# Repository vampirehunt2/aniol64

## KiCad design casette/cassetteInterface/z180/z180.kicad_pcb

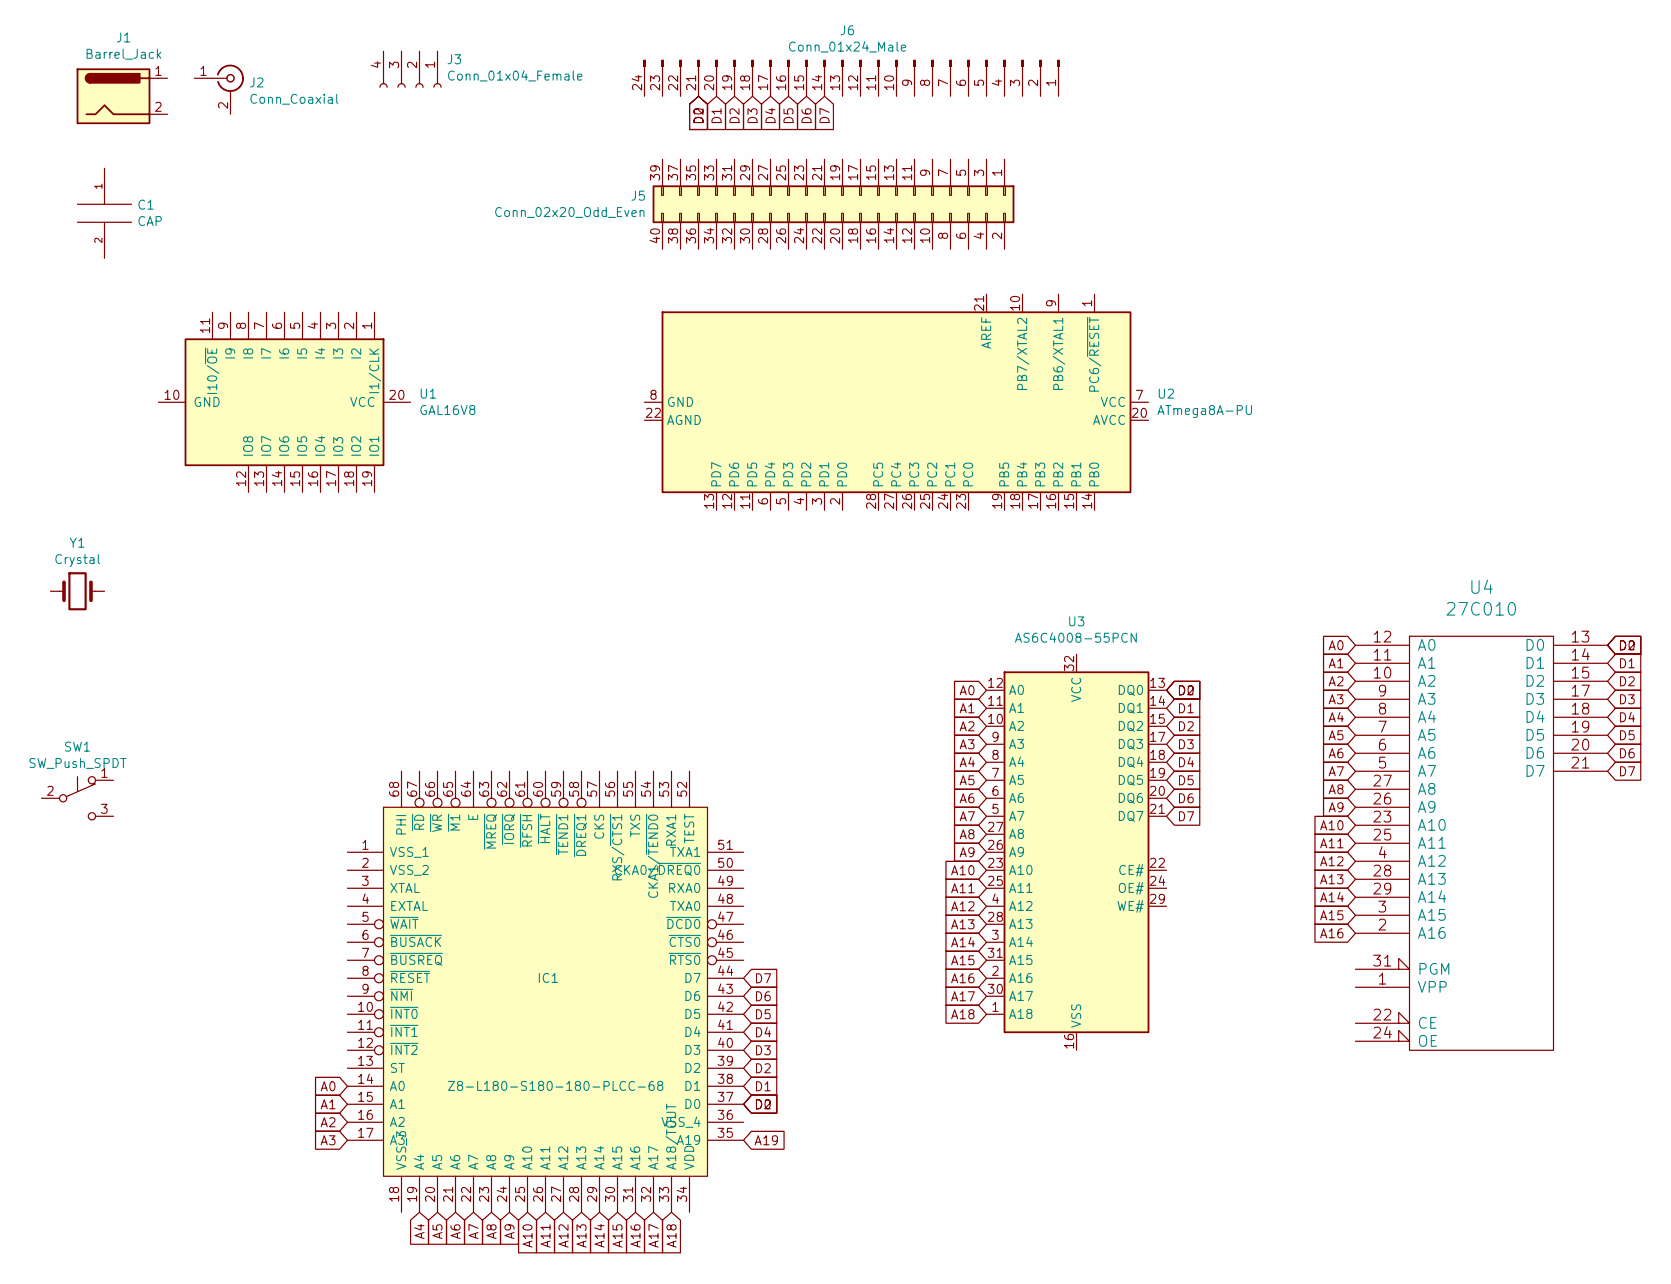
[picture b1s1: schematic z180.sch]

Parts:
C1: CAP; CP_Radial_D10.0mm_P5.00mm_P7.50mm
IC1: Z8-L180-S180-180-PLCC-68; PLCC-68; Manufacturer_Part_Number Z8S18033VSG; Mouser Part Number 692-Z8S18033VSG
J1: Barrel_Jack; BarrelJack_Horizontal
J2: Conn_Coaxial; SMA_Amphenol_132203-12_Horizontal
J3: Conn_01x04_Female; PinHeader_1x04_P2.54mm_Horizontal
J5: Conn_02x20_Odd_Even; PinHeader_2x20_P2.54mm_Vertical_SMD
J6: Conn_01x24_Male; PinHeader_1x24_P2.54mm_Horizontal
SW1: SW_Push_SPDT; SW_Tactile_SKHH_Angled
U1: GAL16V8; DIP-20_W7.62mm_Socket
U2: ATmega8A-PU; DIP-28_W7.62mm
U3: AS6C4008-55PCN; DIP-32_W15.24mm
U4: 27C010; DIP-32_W15.24mm
Y1: Crystal; Crystal_AT310_D3.0mm_L10.0mm_Vertical

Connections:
A0: IC1.14 (A0), U3.12 (A0), U4.12 (A0)
A1: IC1.15 (A1), U3.11 (A1), U4.11 (A1)
A2: IC1.16 (A2), U3.10 (A2), U4.10 (A2)
A3: IC1.17 (A3), U3.9 (A3), U4.9 (A3)
A4: IC1.19 (A4), U3.8 (A4), U4.8 (A4)
A5: IC1.20 (A5), U3.7 (A5), U4.7 (A5)
A6: IC1.21 (A6), U3.6 (A6), U4.6 (A6)
A7: IC1.22 (A7), U3.5 (A7), U4.5 (A7)
A8: IC1.23 (A8), U3.27 (A8), U4.27 (A8)
A9: IC1.24 (A9), U3.26 (A9), U4.26 (A9)
A10: IC1.25 (A10), U3.23 (A10), U4.23 (A10)
A11: IC1.26 (A11), U3.25 (A11), U4.25 (A11)
A12: IC1.27 (A12), U3.4 (A12), U4.4 (A12)
A13: IC1.28 (A13), U3.28 (A13), U4.28 (A13)
A14: IC1.29 (A14), U3.3 (A14), U4.29 (A14)
A15: IC1.30 (A15), U3.31 (A15), U4.3 (A15)
A16: IC1.31 (A16), U3.2 (A16), U4.2 (A16)
A17: IC1.32 (A17), U3.30 (A17)
A18: IC1.33 (A18/TOUT), U3.1 (A18)
D0: IC1.37 (D0), IC1.39 (D2), J6.19, J6.21, U3.13 (DQ0), U3.15 (DQ2), U4.13 (D0), U4.15 (D2)
D1: IC1.38 (D1), J6.20, U3.14 (DQ1), U4.14 (D1)
D3: IC1.40 (D3), J6.18, U3.17 (DQ3), U4.17 (D3)
D4: IC1.41 (D4), J6.17, U3.18 (DQ4), U4.18 (D4)
D5: IC1.42 (D5), J6.16, U3.19 (DQ5), U4.19 (D5)
D6: IC1.43 (D6), J6.15, U3.20 (DQ6), U4.20 (D6)
D7: IC1.44 (D7), J6.14, U3.21 (DQ7), U4.21 (D7)

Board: 2 copper layers, 13 parts (0 on the bottom side), 26 nets, no tracks yet.

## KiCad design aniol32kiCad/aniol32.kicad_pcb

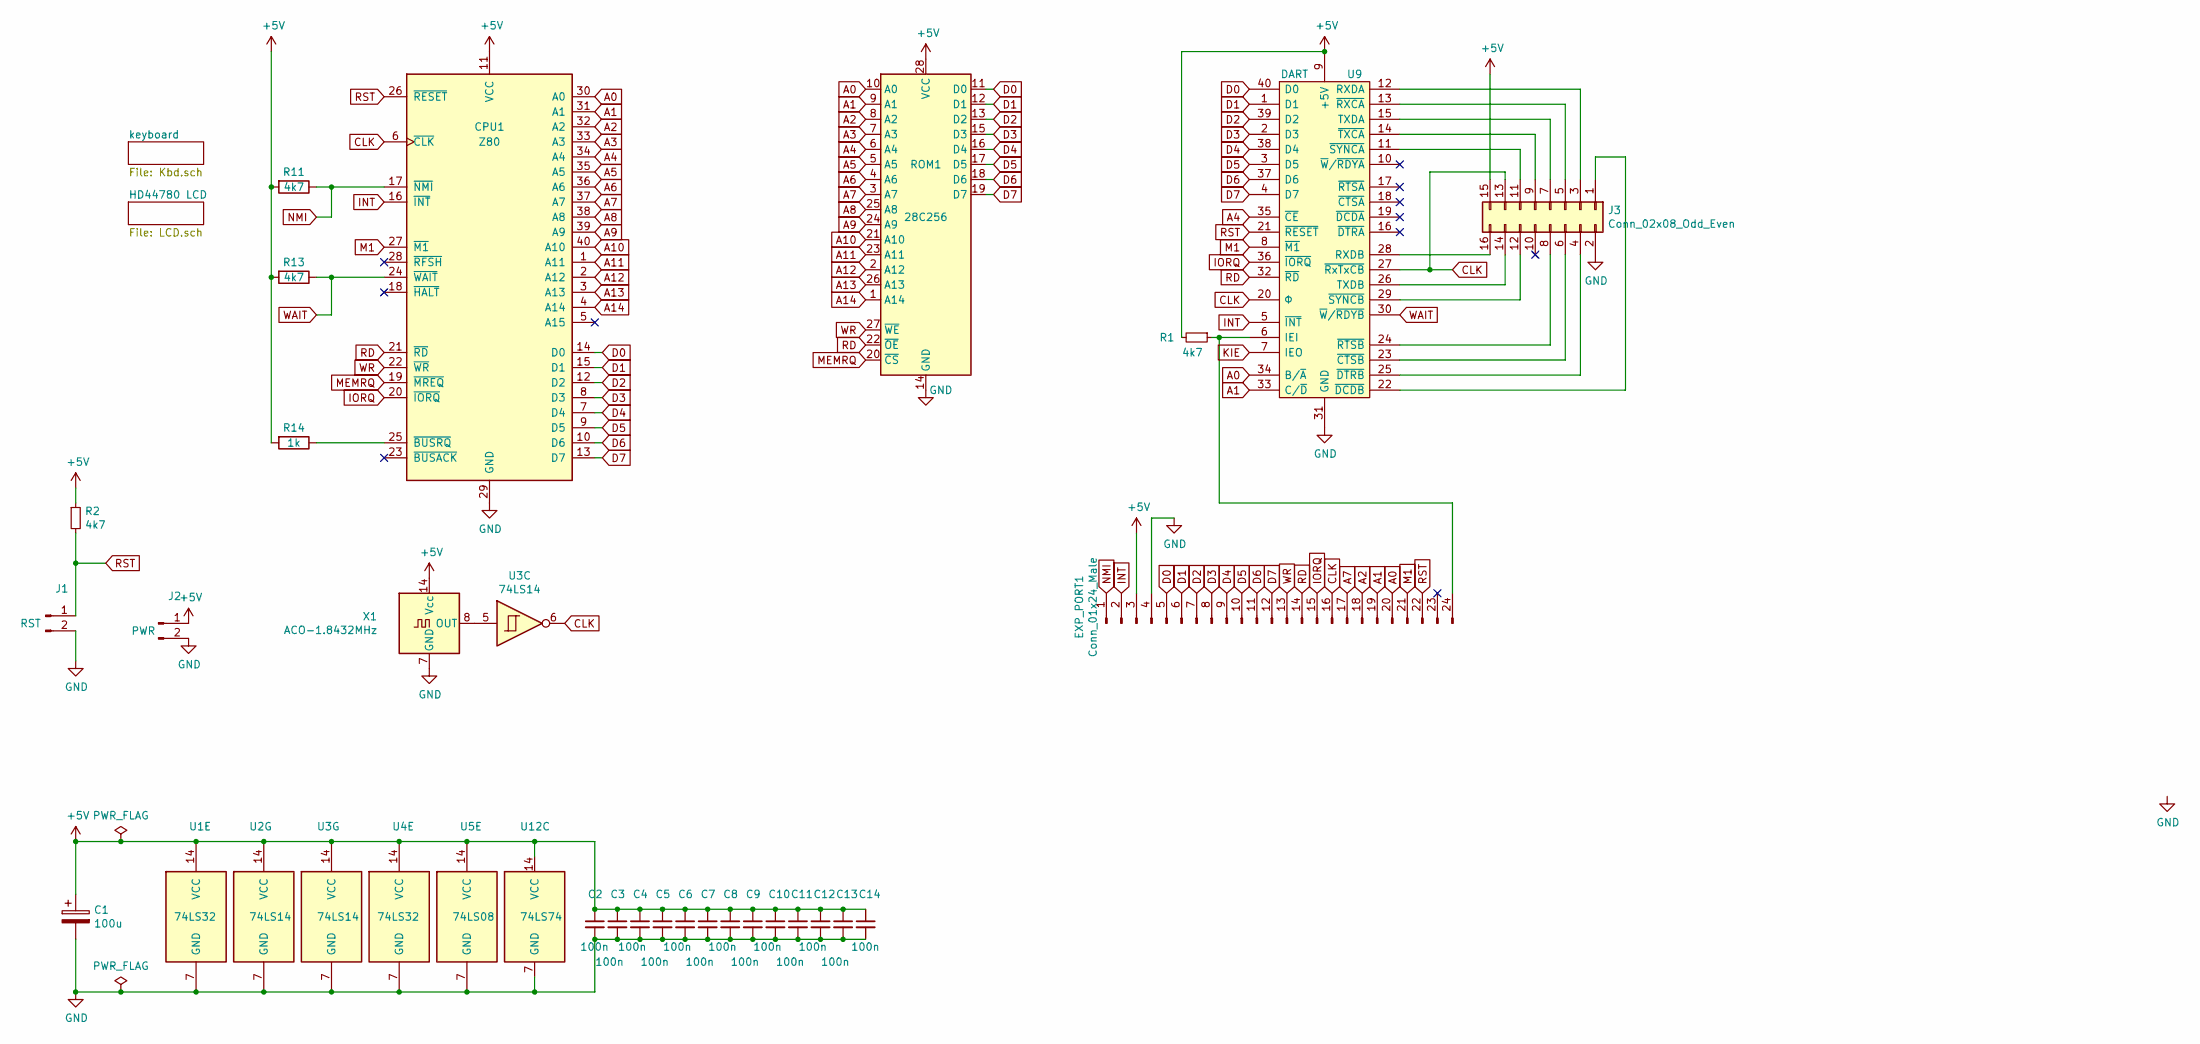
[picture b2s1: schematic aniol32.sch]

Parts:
C1: 100u; CP_Radial_D14.0mm_P7.50mm
C2, C3, C4, C5, C6, C7, C8, C9, C10, C11, C12, C13, C14: 100n; C_Disc_D5.0mm_W2.5mm_P5.00mm
CPU1: Z80; DIP-40_W15.24mm_Socket
EXP_PORT1: Conn_01x24_Male; PinHeader_1x24_P2.54mm_Horizontal
J1: RST; PinHeader_1x02_P2.54mm_Vertical
J2: PWR; PinHeader_1x02_P2.54mm_Vertical
J3: Conn_02x08_Odd_Even; PinSocket_2x08_P2.54mm_Horizontal
R1, R2, R11, R13: 4k7; R_Axial_DIN0207_L6.3mm_D2.5mm_P7.62mm_Horizontal
R14: 1k; R_Axial_DIN0207_L6.3mm_D2.5mm_P7.62mm_Horizontal
ROM1: 28C256; DIP-28_W15.24mm_Socket
U1, U4: 74LS32; DIP-14_W7.62mm_Socket
U2, U3: 74LS14; DIP-14_W7.62mm_Socket
U5: 74LS08; DIP-14_W7.62mm_Socket
U9: DART; DIP-40_W15.24mm_Socket; Manufacturer_Part_Number Z84C4206PEG; Mouser Part Number 692-Z84C4206PEG
U12: 74LS74; DIP-14_W7.62mm_Socket
X1: ACO-1.8432MHz; Oscillator_DIP-14

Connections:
+5V: C1.1, C2.1, C3.1, C4.1, C5.1, C6.1, C7.1, C8.1, C9.1, C10.1, C11.1, C12.1, C13.1, C14.1, CPU1.11 (VCC), EXP_PORT1.3, J2.1, J3.15, R1.2, R2.1, R11.2, R13.2, R14.2, ROM1.28 (VCC), U1.14 (VCC), U2.14 (VCC), U3.14 (VCC), U4.14 (VCC), U5.14 (VCC), U9.9 (+5V), U12.14 (VCC), X1.14 (Vcc); also elsewhere on the board
A0: CPU1.30 (A0), EXP_PORT1.20, ROM1.10 (A0), U9.34 (B/~A); also elsewhere on the board
A1: CPU1.31 (A1), EXP_PORT1.19, ROM1.9 (A1), U9.33 (C/~D); also elsewhere on the board
A2: CPU1.32 (A2), EXP_PORT1.18, ROM1.8 (A2)
A3: CPU1.33 (A3), ROM1.7 (A3), U1.10
A4: CPU1.34 (A4), ROM1.6 (A4), U9.35 (~CE)
A5: CPU1.35 (A5), ROM1.5 (A5)
A6: CPU1.36 (A6), ROM1.4 (A6); also elsewhere on the board
A7: CPU1.37 (A7), EXP_PORT1.17, ROM1.3 (A7)
A8: CPU1.38 (A8), ROM1.25 (A8)
A9: CPU1.39 (A9), ROM1.24 (A9)
A10: CPU1.40 (A10), ROM1.21 (A10)
A11: CPU1.1 (A11), ROM1.23 (A11)
A12: CPU1.2 (A12), ROM1.2 (A12)
A13: CPU1.3 (A13), ROM1.26 (A13)
A14: CPU1.4 (A14), ROM1.1 (A14)
CLK: CPU1.6 (~CLK~), EXP_PORT1.16, J3.13, U3.6, U9.20 (Φ), U9.27 (~RxTxCB); also elsewhere on the board
D0: CPU1.14 (D0), EXP_PORT1.5, ROM1.11 (D0), U9.40 (D0); also elsewhere on the board
D1: CPU1.15 (D1), EXP_PORT1.6, ROM1.12 (D1), U9.1 (D1); also elsewhere on the board
D2: CPU1.12 (D2), EXP_PORT1.7, ROM1.13 (D2), U9.39 (D2); also elsewhere on the board
D3: CPU1.8 (D3), EXP_PORT1.8, ROM1.15 (D3), U9.2 (D3); also elsewhere on the board
D4: CPU1.7 (D4), EXP_PORT1.9, ROM1.16 (D4), U9.38 (D4); also elsewhere on the board
D5: CPU1.9 (D5), EXP_PORT1.10, ROM1.17 (D5), U9.3 (D5); also elsewhere on the board
D6: CPU1.10 (D6), EXP_PORT1.11, ROM1.18 (D6), U9.37 (D6); also elsewhere on the board
D7: CPU1.13 (D7), EXP_PORT1.12, ROM1.19 (D7), U9.4 (D7); also elsewhere on the board
GND: C1.2, C2.2, C3.2, C4.2, C5.2, C6.2, C7.2, C8.2, C9.2, C10.2, C11.2, C12.2, C13.2, C14.2, CPU1.29 (GND), EXP_PORT1.4, J1.2, J2.2, J3.2, ROM1.14 (GND), U1.7 (GND), U2.7 (GND), U3.7 (GND), U4.7 (GND), U5.7 (GND), U9.31 (GND), U12.7 (GND), X1.7 (GND); also elsewhere on the board
INT: CPU1.16 (~INT~), EXP_PORT1.2, U9.5 (~INT); also elsewhere on the board
IORQ: CPU1.20 (~IORQ~), EXP_PORT1.15, U1.9, U9.36 (~IORQ); also elsewhere on the board
KIE: U9.7 (IEO); also elsewhere on the board
LCDE: U2.4; also elsewhere on the board
M1: CPU1.27 (~M1~), EXP_PORT1.21, U9.8 (~M1); also elsewhere on the board
MEMRQ: CPU1.19 (~MREQ~), ROM1.20 (~CS)
NMI: CPU1.17 (~NMI~), EXP_PORT1.1, R11.1; also elsewhere on the board
unnamed: CPU1.25 (~BUSRQ~), R14.1
unnamed: EXP_PORT1.24, R1.1, U9.6 (IEI)
unnamed: J3.3, U9.12 (RXDA)
unnamed: J3.4, U9.25 (~DTRB)
unnamed: J3.5, U9.13 (~RXCA)
unnamed: J3.6, U9.23 (~CTSB)
unnamed: J3.7, U9.15 (TXDA)
unnamed: J3.8, U9.24 (~RTSB)
unnamed: J3.9, U9.14 (~TXCA)
unnamed: J3.11, U9.11 (~SYNCA)
unnamed: J3.12, U9.29 (~SYNCB)
unnamed: J3.16, U9.28 (RXDB)
unnamed: U1.11, U2.3
unnamed: U1.8, U1.12
unnamed: U1.13, U5.11
unnamed: U3.5, X1.8 (OUT)
RD: CPU1.21 (~RD~), EXP_PORT1.14, ROM1.22 (~OE), U5.12, U9.32 (~RD); also elsewhere on the board
RST: CPU1.26 (~RESET~), EXP_PORT1.22, J1.1, R2.2, U9.21 (~RESET); also elsewhere on the board
WAIT: CPU1.24 (~WAIT~), R13.1, U9.30 (~W~/~RDYB)
WR: CPU1.22 (~WR~), EXP_PORT1.13, ROM1.27 (~WE), U5.13; also elsewhere on the board

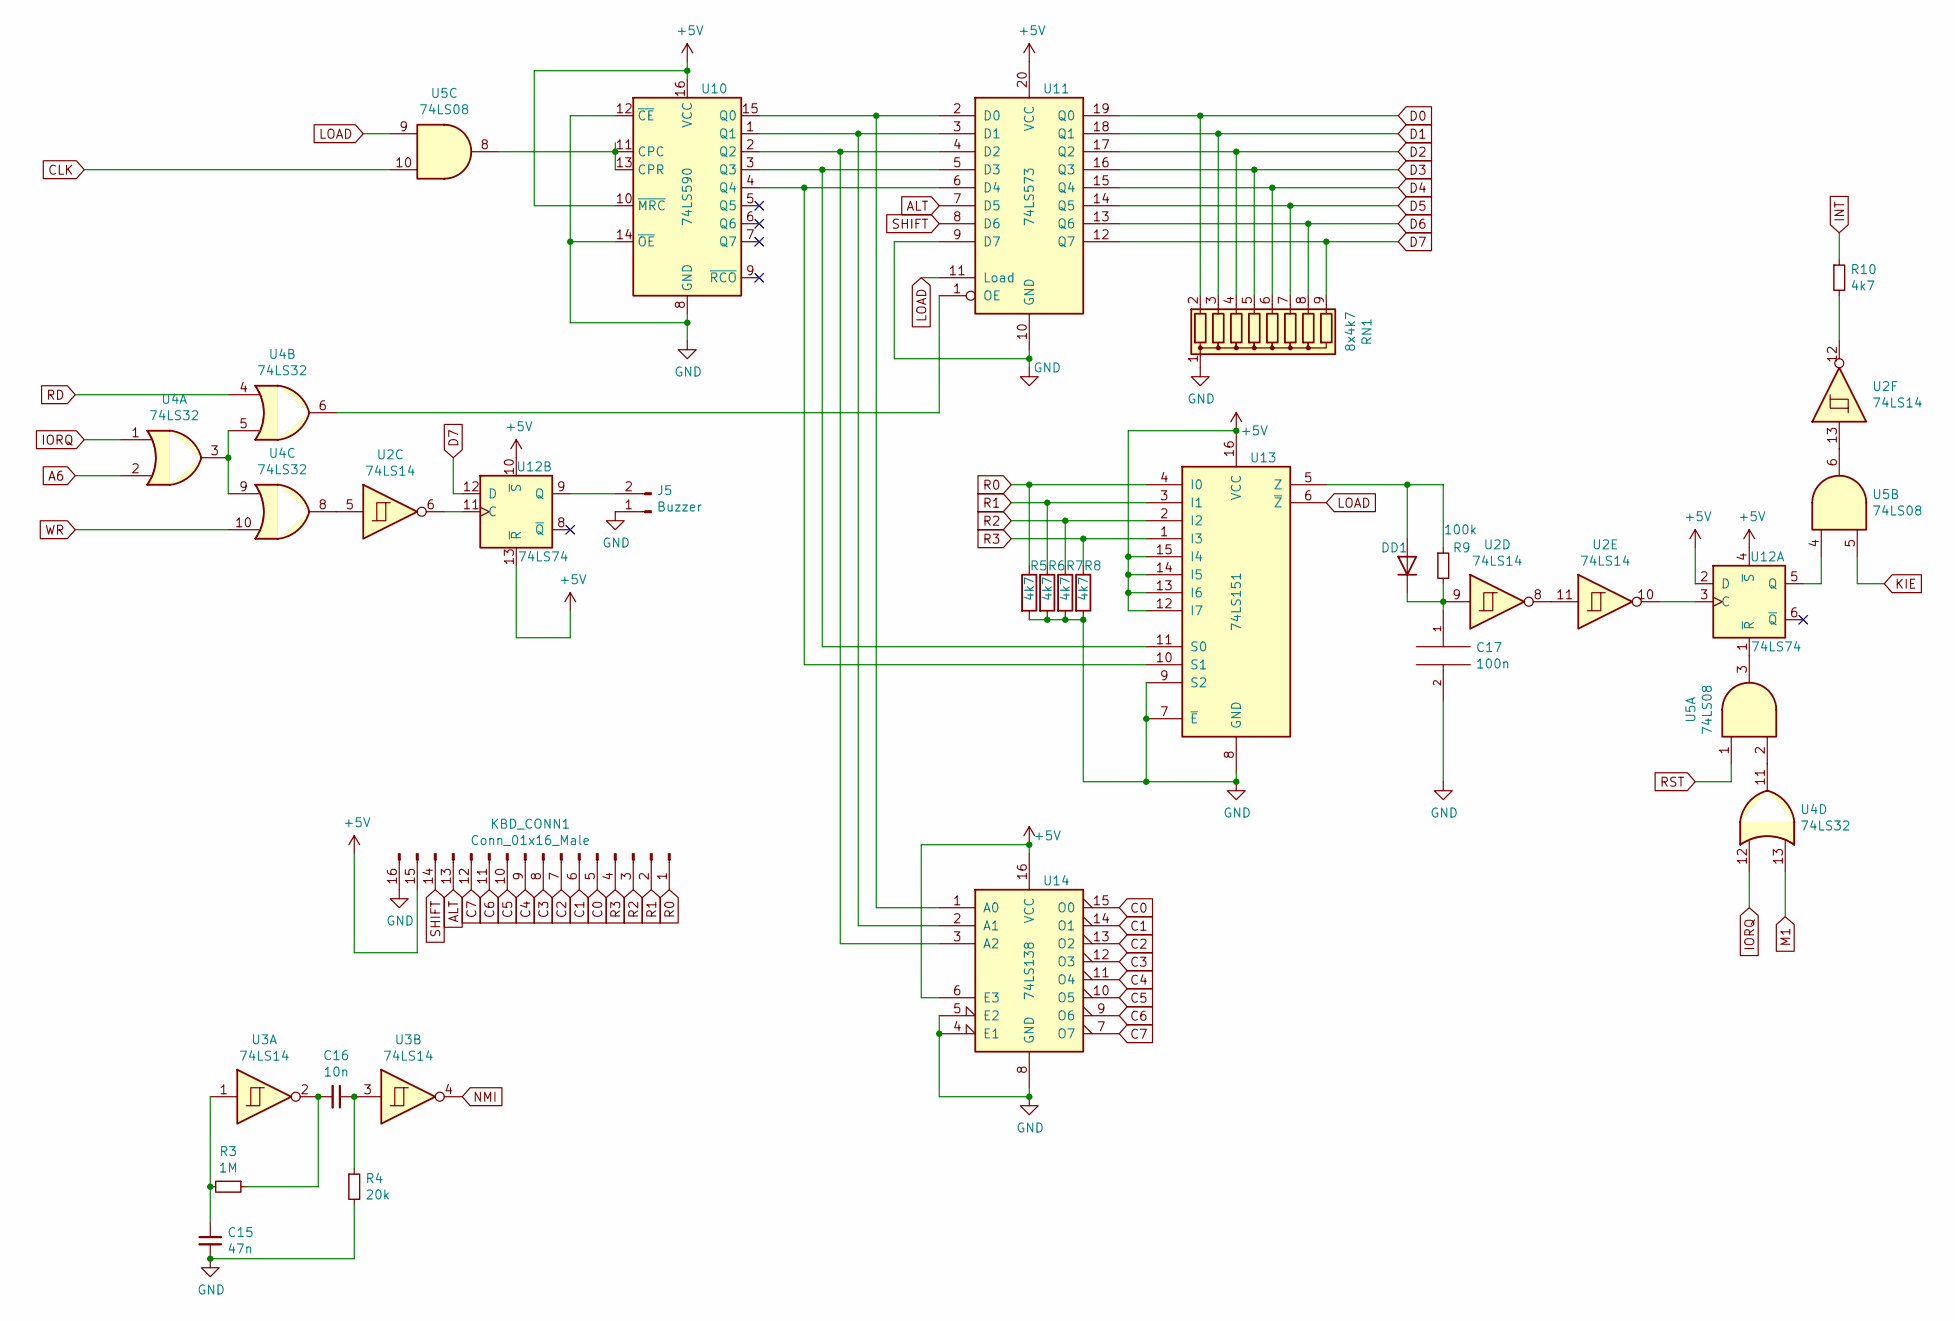
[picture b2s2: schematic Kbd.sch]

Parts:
C15: 47n; C_Disc_D5.0mm_W2.5mm_P5.00mm
C16: 10n; C_Disc_D5.0mm_W2.5mm_P5.00mm
C17: 100n; C_Disc_D5.0mm_W2.5mm_P5.00mm
D1: D; D_5KPW_P7.62mm_Vertical_AnodeUp
J5: Buzzer; PinHeader_1x02_P2.54mm_Vertical
KBD_CONN1: Conn_01x16_Male; PinHeader_1x16_P2.54mm_Vertical
R3: 1M; R_Axial_DIN0207_L6.3mm_D2.5mm_P7.62mm_Horizontal
R4: 20k; R_Axial_DIN0207_L6.3mm_D2.5mm_P7.62mm_Horizontal
R5, R6, R7, R8, R10: 4k7; R_Axial_DIN0207_L6.3mm_D2.5mm_P7.62mm_Horizontal
R9: 100k; R_Axial_DIN0207_L6.3mm_D2.5mm_P7.62mm_Horizontal
RN1: 8x4k7; R_Array_SIP9
U2, U3: 74LS14; DIP-14_W7.62mm_Socket
U4: 74LS32; DIP-14_W7.62mm_Socket
U5: 74LS08; DIP-14_W7.62mm_Socket
U10: 74LS590; DIP-16_W7.62mm_Socket
U11: 74LS573; DIP-20_W7.62mm_Socket
U12: 74LS74; DIP-14_W7.62mm_Socket
U13: 74LS151; DIP-16_W7.62mm_Socket
U14: 74LS138; DIP-16_W7.62mm_Socket

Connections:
+5V: KBD_CONN1.15, U10.10 (~MRC), U10.16 (VCC), U11.20 (VCC), U12.2 (D), U12.4 (~S), U12.10 (~S), U12.13 (~R), U13.12 (I7), U13.13 (I6), U13.14 (I5), U13.15 (I4), U13.16 (VCC), U14.6 (E3), U14.16 (VCC); also elsewhere on the board
A6: U4.2; also elsewhere on the board
ALT: KBD_CONN1.13, U11.7 (D5)
C0: KBD_CONN1.5, U14.15 (O0)
C1: KBD_CONN1.6, U14.14 (O1)
C2: KBD_CONN1.7, U14.13 (O2)
C3: KBD_CONN1.8, U14.12 (O3)
C4: KBD_CONN1.9, U14.11 (O4)
C5: KBD_CONN1.10, U14.10 (O5)
C6: KBD_CONN1.11, U14.9 (O6)
C7: KBD_CONN1.12, U14.7 (O7)
CLK: U5.10; also elsewhere on the board
D0: RN1.2 (R1), U11.19 (Q0); also elsewhere on the board
D1: RN1.3 (R2), U11.18 (Q1); also elsewhere on the board
D2: RN1.4 (R3), U11.17 (Q2); also elsewhere on the board
D3: RN1.5 (R4), U11.16 (Q3); also elsewhere on the board
D4: RN1.6 (R5), U11.15 (Q4); also elsewhere on the board
D5: RN1.7 (R6), U11.14 (Q5); also elsewhere on the board
D6: RN1.8 (R7), U11.13 (Q6); also elsewhere on the board
D7: RN1.9 (R8), U11.12 (Q7), U12.12 (D); also elsewhere on the board
GND: C15.2, C17.2, J5.1, KBD_CONN1.16, R4.2, R5.2, R6.2, R7.2, R8.2, RN1.1 (common), U10.8 (GND), U10.12 (~CE), U10.14 (~OE), U11.9 (D7), U11.10 (GND), U13.7 (~E), U13.8 (GND), U13.9 (S2), U14.4 (E1), U14.5 (E2), U14.8 (GND); also elsewhere on the board
INT: R10.1; also elsewhere on the board
IORQ: U4.1, U4.12; also elsewhere on the board
KIE: U5.5; also elsewhere on the board
LCDE: U2.4; also elsewhere on the board
LOAD: U5.9, U11.11 (Load), U13.6 (~Z)
M1: U4.13; also elsewhere on the board
NMI: U3.4; also elsewhere on the board
unnamed: C15.1, R3.2, U3.1
unnamed: C16.1, R4.1, U3.3
unnamed: C16.2, R3.1, U3.2
unnamed: C17.1, D1.1 (K), R9.2, U2.9
unnamed: D1.2 (A), R9.1, U13.5 (Z)
unnamed: J5.2, U12.9 (Q)
unnamed: R10.2, U2.12
unnamed 63: U2.3; also elsewhere on the board
unnamed 65: U5.11; also elsewhere on the board
unnamed: U2.5, U4.8
unnamed: U2.8, U2.11
unnamed: U2.13, U5.6
unnamed: U4.3, U4.5, U4.9
unnamed: U4.11, U5.2
unnamed: U10.1 (Q1), U11.3 (D1), U14.2 (A1)
unnamed: U10.2 (Q2), U11.4 (D2), U14.3 (A2)
unnamed: U10.3 (Q3), U11.5 (D3), U13.11 (S0)
unnamed: U10.4 (Q4), U11.6 (D4), U13.10 (S1)
unnamed: U5.8, U10.11 (CPC), U10.13 (CPR)
unnamed: U10.15 (Q0), U11.2 (D0), U14.1 (A0)
unnamed: U4.6, U11.1 (OE)
unnamed: U5.3, U12.1 (~R)
unnamed: U2.10, U12.3 (C)
unnamed: U5.4, U12.5 (Q)
unnamed: U2.6, U12.11 (C)
R0: KBD_CONN1.1, R5.1, U13.4 (I0)
R1: KBD_CONN1.2, R6.1, U13.3 (I1)
R2: KBD_CONN1.3, R7.1, U13.2 (I2)
R3: KBD_CONN1.4, R8.1, U13.1 (I3)
RD: U4.4, U5.12; also elsewhere on the board
RST: U5.1; also elsewhere on the board
SHIFT: KBD_CONN1.14, U11.8 (D6)
WR: U4.10, U5.13; also elsewhere on the board

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
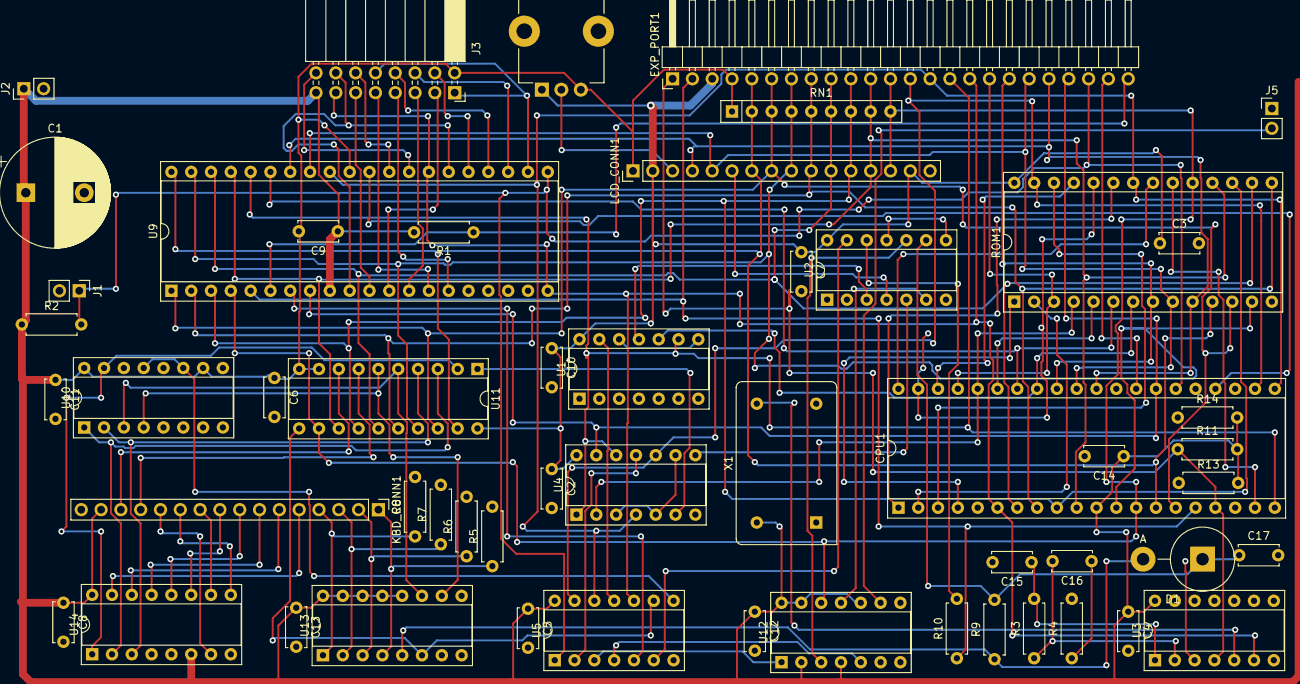
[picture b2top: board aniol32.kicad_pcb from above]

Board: 2 copper layers, 54 parts (0 on the bottom side), 94 nets.

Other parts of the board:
LCD_CONN1: Conn_01x16_Male; PinHeader_1x16_P2.54mm_Vertical
RV1: R_POT_TRIM; Potentiometer_TT_P0915N

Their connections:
+5V: LCD_CONN1.2, LCD_CONN1.15, RV1.1; also elsewhere on the board
A0: LCD_CONN1.4; also elsewhere on the board
A1: LCD_CONN1.5; also elsewhere on the board
CONTRAST: LCD_CONN1.3, RV1.2
D0: LCD_CONN1.7; also elsewhere on the board
D1: LCD_CONN1.8; also elsewhere on the board
D2: LCD_CONN1.9; also elsewhere on the board
D3: LCD_CONN1.10; also elsewhere on the board
D4: LCD_CONN1.11; also elsewhere on the board
D5: LCD_CONN1.12; also elsewhere on the board
D6: LCD_CONN1.13; also elsewhere on the board
D7: LCD_CONN1.14; also elsewhere on the board
GND: LCD_CONN1.1, LCD_CONN1.16, RV1.3; also elsewhere on the board
LCDE: LCD_CONN1.6; also elsewhere on the board

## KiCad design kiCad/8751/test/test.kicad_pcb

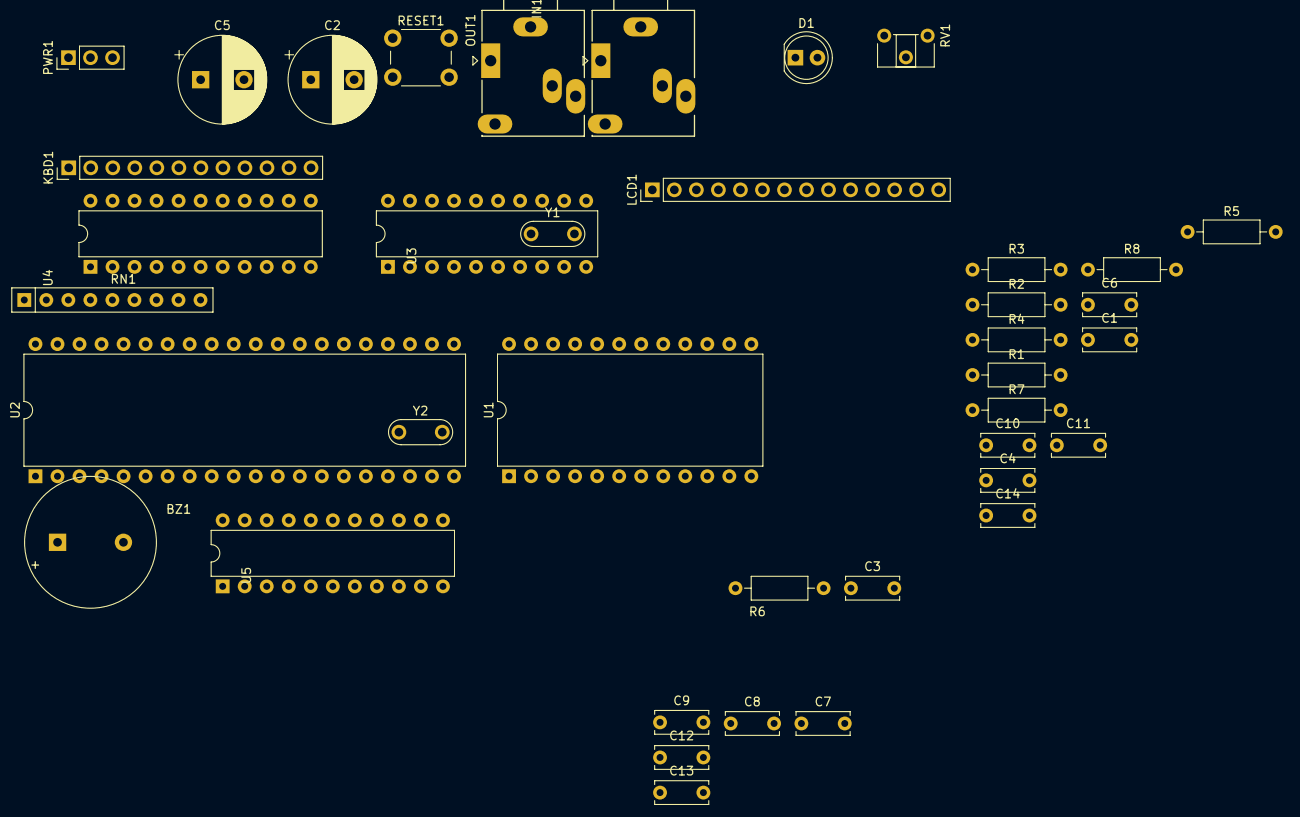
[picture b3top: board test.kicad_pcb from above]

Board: 2 copper layers, 39 parts (0 on the bottom side), 67 nets, no tracks yet.

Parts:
BZ1: Buzzer; Buzzer_15x7.5RM7.6
C1, C6, C7, C9, C10, C12, C13, C14: 100n; C_Disc_D6.0mm_W2.5mm_P5.00mm
C2, C5: C_Polarized; CP_Radial_D10.0mm_P5.00mm
C3, C4: 27p; C_Disc_D6.0mm_W2.5mm_P5.00mm
C8, C11: 18p; C_Disc_D6.0mm_W2.5mm_P5.00mm
D1: LED; LED_D5.0mm
IN1: AudioJack3; Jack_3.5mm_Ledino_KB3SPRS_Horizontal
KBD1: KBD; PinHeader_1x12_P2.54mm_Vertical
LCD1: LCD; PinHeader_1x14_P2.54mm_Vertical
OUT1: AudioJack3; Jack_3.5mm_Ledino_KB3SPRS_Horizontal
PWR1: Conn_01x03_Male; PinHeader_1x03_P2.54mm_Vertical
R1: 10k; R_Axial_DIN0207_L6.3mm_D2.5mm_P10.16mm_Horizontal
R2, R3: R_Small; R_Axial_DIN0207_L6.3mm_D2.5mm_P10.16mm_Horizontal
R4: 600; R_Axial_DIN0207_L6.3mm_D2.5mm_P10.16mm_Horizontal
R5, R6, R7, R8: 1k; R_Axial_DIN0207_L6.3mm_D2.5mm_P10.16mm_Horizontal
RESET1: SW_SPST; SW_PUSH_6mm
RN1: 470; R_Array_SIP9
RV1: 5k; Potentiometer_ACP_CA6-H2,5_Horizontal
U1: 6116; DIP-24_W15.24mm
U2: 87c51; DIP-40_W15.24mm
U3: MC14544x; DIP-20_W7.62mm
U4: 74LS541; DIP-22_W7.62mm
U5: 74LS574; DIP-22_W7.62mm
Y1: 3.58MHz; Resonator-2Pin_W7.0mm_H2.5mm
Y2: 12MHz; Resonator-2Pin_W7.0mm_H2.5mm

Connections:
+5V: C2.1, C7.1, C9.1, C12.1, C13.1, C14.1, LCD1.2, R3.2, RESET1.2 (B), RN1.1 (common), RV1.1, U1.24 (VCC), U2.31 (EA#/VPP), U2.40 (VCC), U3.6 (VDD), U4.20 (VCC), U5.20 (VCC)
/A0: R5.1, U1.8 (A0), U5.19 (Q0)
/A1: R6.1, U1.7 (A1), U5.18 (Q1)
/A2: R7.1, U1.6 (A2), U5.17 (Q2)
/A3: R8.1, U1.5 (A3), U5.16 (Q3)
/A4: U1.4 (A4), U5.15 (Q4)
/A5: U1.3 (A5), U5.14 (Q5)
/A6: U1.2 (A6), U5.13 (Q6)
/A7: U1.1 (A7), U5.12 (Q7)
/A8: U1.23 (A8), U2.21 (P2.0_(A8))
/A9: U1.22 (A9), U2.22 (P2.1_(A9))
/A10: U1.19 (A10), U2.23 (P2.2_(A10))
/D0: RN1.2 (R1), U1.9 (Q0), U2.39 (P0.0_(AD0)), U4.18 (Y0), U5.2 (D0)
/D1: RN1.3 (R2), U1.10 (Q1), U2.38 (P0.1_(AD1)), U4.17 (Y1), U5.3 (D1)
/D2: RN1.4 (R3), U1.11 (Q2), U2.37 (P0.2_(AD2)), U4.16 (Y2), U5.4 (D2)
/D3: RN1.5 (R4), U1.13 (Q3), U2.36 (P0.3_(AD3)), U4.15 (Y3), U5.5 (D3)
/D4: RN1.6 (R5), U1.14 (Q4), U2.35 (P0.4_(AD4)), U4.14 (Y4), U5.6 (D4)
/D5: RN1.7 (R6), U1.15 (Q5), U2.34 (P0.5_(AD5)), U4.13 (Y5), U5.7 (D5)
/D6: RN1.8 (R7), U1.16 (Q6), U2.33 (P0.6_(AD6)), U4.12 (Y6), U5.8 (D6)
/D7: RN1.9 (R8), U1.17 (Q7), U2.32 (P0.7_(AD7)), U4.11 (Y7), U5.9 (D7)
GND: BZ1.2 (+), C1.1, C3.2, C4.2, C5.2, C6.2, C7.2, C8.2, C10.2, C11.2, C12.2, C13.2, C14.2, IN1.S, LCD1.1, OUT1.S, PWR1.2, R1.2, R2.2, RV1.3, U1.12 (GND), U2.20 (GND), U3.2 (~LB), U3.12 (VSS), U3.14 (SQT), U4.10 (GND), U5.1 (OE), U5.10 (GND)
KBDEN: U2.27 (P2.6_(A14)), U4.1 (G1)
LCDEN: LCD1.6, U2.12 ((INT0#)_P3.2)
unnamed: BZ1.1 (-), U2.13 ((INT1#)_P3.3)
unnamed: C1.2, U3.4 (CDT)
unnamed: C3.1, U3.8 (XOUT), Y1.1
unnamed: C4.1, U3.9 (XIN), Y1.2
unnamed: C5.1, D1.2 (A), PWR1.1
unnamed: C6.1, U3.10 (FB)
unnamed: C8.1, U2.18 (XTAL2), Y2.1
unnamed: C9.2, C10.1, U3.18 (EXL), U3.19 (VAG)
unnamed: C11.1, U2.19 (XTAL1), Y2.2
unnamed: D1.1 (K), R2.1
unnamed: IN1.T, R4.2, U3.15 (RxA2)
unnamed: KBD1.1, R5.2
unnamed: KBD1.2, R6.2
unnamed: KBD1.3, R7.2
unnamed: KBD1.4, R8.2
unnamed: KBD1.5, U4.2 (A0)
unnamed: KBD1.6, U4.3 (A1)
unnamed: KBD1.7, U4.4 (A2)
unnamed: KBD1.8, U4.5 (A3)
unnamed: KBD1.9, U4.6 (A4)
unnamed: KBD1.10, U4.7 (A5)
unnamed: KBD1.11, U4.8 (A6)
unnamed: KBD1.12, U4.9 (A7)
unnamed: LCD1.3, RV1.2
unnamed: LCD1.7, U2.1 (P1.0)
unnamed: LCD1.8, U2.2 (P1.1)
unnamed: LCD1.9, U2.3 (P1.2)
unnamed: LCD1.10, U2.4 (P1.3)
unnamed: LCD1.11, U2.5 (P1.4)
unnamed: LCD1.12, U2.6 (P1.5)
unnamed: LCD1.13, U2.7 (P1.6)
unnamed: LCD1.14, U2.8 (P1.7)
unnamed: OUT1.T, U3.17 (TxA)
unnamed: R3.1, U3.20 (TLA)
unnamed: R4.1, U3.16 (RxA1)
unnamed: U2.30 (ALT/PROG#), U5.11 (Cp)
RAMCS: U1.18 (~CS), U2.28 (P2.7_(A15))
RD: U1.20 (~OE), U2.17 ((RD#)_P3.7), U4.19 (G2)
RS: LCD1.4, U2.14 ((T0)_P3.4)
RST: C2.2, R1.1, RESET1.1 (A), U2.9 (RESET)
RW: LCD1.5, U2.15 ((T1)_P3.5), U3.13 (MODE)
Rx: U2.10 ((RXD)_P3.0), U3.5 (RxD)
Tx: U2.11 ((TXD)_P3.1), U3.11 (TxD)
WR: U1.21 (~WE), U2.16 ((WR#)_P3.6)

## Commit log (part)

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2022-04-23 adding the math module
2022-04-24 added binary formatting
2022-04-24 optimised decimal parsing
2022-04-24 added overflow checking to decimal parsing
    but it doesn't work yet because u16_mul doesn't report overflow correctly
2022-04-27 working on VGA code
2022-04-28 initial commit of the 640 branch
2022-05-05 switched completely from LCD to VGA
2022-05-07 fixed a bug where a blank line was written after the beep command
2022-05-11 moved dev drivers and utils to separate folders
2022-05-30 Compact Flash interface
2022-05-31 added an option to disable echo
2022-05-31 test of custom NMI handler
2022-06-02 refactoring list
2022-06-02 Added a procedure to print out the CF signature
2022-06-06 added a get function to the list
2022-06-10 created reverse polish notation calculator
2022-06-22 loading and saving sectors
2022-06-26 make snake always start from the middle of the screen
2022-06-26 fixed a bug in ls command calling
2022-06-28 added mkdir command
2022-06-28 removed many CP 0s after str_cmp calls
2022-07-02 added cd command. added direct set to mon
    https://github.com/vampirehunt2/aniol64/issues/10
2022-09-11 Added basic PS2 keyboard support
2022-09-11 SHIFT key support added for ps2 keyboard
2022-09-18 fixed a bug in ls which prevented files from being listed
2022-09-18 fixed a bug which caused 'touch' to not work at all
2022-09-18 added support for file sizes in 'ls'
2022-10-19 8088 project added
2022-11-09 stable with ps2 support
2022-11-09 establishing a baseline after branching from aniol64PS2
2022-11-19 Added AniolZ180 CUPL project
2022-11-21 changed VGA Gen Gen software to prevent skewed first lines
2022-11-21 Created A54 frontplate
2022-11-23 Fixed a bug in VGAGenGen horizontal reset
2023-01-02 Updated schematic of the CP/M card
2023-01-02 update gitignore to ignore eclipse metadata
2023-01-06 Update rogue.asm
    optimised performance of random dungeon generator
2023-01-07 introduced corridor generation
2023-01-08 refactored the room data structure
2023-01-09 moved cursror init to they keyboard modules
2023-01-09 temporarily removed test command from cmd
2023-01-09 changed the size of the file table
    63 sectors now instead of 28
    this is a preparation for logical disks
2023-01-09 created tool to visualise the vga video memory from emulator
2023-01-09 test and doc updates
2023-01-09 refactored VGA public function names
2023-01-21 stable with PS2 keyboard and TellyMate support
2023-01-21 PS2 keyboard now consumes (and ignores) the BATcode on init
2023-01-24 Update Design.html
    Corrected the input/output pin descriptions in the expansion interface.
2023-01-24 Added door sanitisation
2023-01-24 cleaned up debug information in list.asm
2023-01-26 Fixed missing Echo initialisation
2023-01-27 Fixed a bug in gotoXY
2023-01-27 enabled snake to work on any resolution
2023-01-28 changed the size of the playfield to fill screen
2023-01-28 Made PS2 readKey to be non-interrupt driven
2023-01-29 Hide the cursor when generating dungeon
2023-01-29 fixed a bug in isAplhanumericCharacter
2023-01-29 added load and cat commands
2023-02-01 introduced fSave, fLoad and cat
2023-02-01 Fixed a typo in FALSE constant in edit.asm
2023-02-04 fixed a bug in delay routines
    1520us delay was only 890us
2023-02-11 Update bzr.asm
    fixed delay bug
2023-02-11 Update tm.asm
    Revert changes related to PS2 keyboard initialisation. This is now completely handled in ps2.asm using DART Channel A only
2023-02-11 Improved LOS and walking
2023-02-12 Added descending by stairs
2023-02-18 adding font generators
2023-02-18 Added error codes and messages
2023-02-18 Skipping the first line of the display to avoid distorsion
2023-02-19 Workaround for a bug in the assember
2023-02-19 simplify the fRad and fWrite routines
2023-02-22 added u16_formatHex
2023-02-22 Added selecting keyword token
2023-02-22 Implemented str_startsWith
2023-02-22 Implemented apl_getOperatorCode
2023-02-25 working apl_getVarCode
2023-02-28 separate handling of brackets
    also, fixed a bug in number processing
2023-03-02 added signed 16 bit parsing and formatting
2023-03-04 converted the code to comply with sjasmplus
2023-03-04 Fixed bugs in negative number parsing in apl
2023-03-10 fix the bug that was causing transmit to not be enabled
2023-03-15 Added cleaniing up old binaries prior to assembly
2023-03-15 Added monster generation
2023-03-19 fixed issues with load and save
    separated dos_load from cmd_load and similarly for save
2023-03-20 fixes for #19 #22
    Loading 0-length files hangs the system #19
    you can cat a nonexistent file #22
2023-03-20 fixed https://github.com/vampirehunt2/aniol64/issues/11
2023-03-22 removed expansion buffering
2023-04-01 added scrolling in edit
2023-04-12 editor somewhat working
2023-04-12 Improvements to multiline commands
2023-04-13 fixed rog: levels lower than 1 are corrupted #25
2023-04-14 edit: ed_end puts the cursor off-screen #29
2023-04-14 fixed edit: deleting the last line causes a crash #27
2023-04-15 Fixed nonsense routine i16_sub
2023-04-15 fixed remove redundant CP 0s after calling str_cmp #7
2023-04-20 removed redundant CP 0 after str_cmp
2023-04-28 moved apl to high ROM
2023-04-28 formatting
2023-05-01 Added pal card driver
2023-06-08 Added tokenizing keywords and build-in functions
2023-06-08 added tar commands
2023-06-08 bytecode for newline should be the same as for :
2023-06-08 Multiple consecutive separators avoidance
2023-06-19 implementing the interpreter
2023-06-19 schematic updates
2023-06-19 comment correction
2023-06-23 Put APL and Run bytecodes in the same place in memory
2023-06-23 Variable assignment
2023-06-29 Square bracket as index operator
2023-06-30 Comparison operators
2023-07-02 ELSE statement
2023-07-03 WHILE loops
2023-07-30 added finding procedure addresses
2023-08-05 Added user calls
2023-09-03 added support for built-in functions in expressions
2023-10-01 Declaring strings
2023-10-29 Assignment to array elements
2023-11-20 Renamed main file to aniol180
2023-11-27 initial booting
2023-12-11 PS2 keyboard draft
2023-12-16 fixed a bug in cassette code
2023-12-16 tokenizing comments
2024-01-15 serial keyboard
2024-01-19 Writing out strings
2024-01-20 added string indexing in expressions
2024-01-20 Assignment to a string element
2024-01-20 Fixed a bug in comment parsing
2024-02-05 Added TinyBasic85
2024-02-05 Added serial kbd source code
2024-02-05 Fixed bugs in the scan table
2024-02-07 added get, put, poke
2024-02-10 added the Delay command
2024-02-13 fixed a bug with cat on vga not printing newlines
2024-02-13 fixed a bug with trim crashing for non-negative numbers
2024-05-19 Adding Tiny BASIC for 8085
2024-05-19 8085 kicad
2024-06-09 added save, reset, seek and fread routines
2024-08-07 DOS functions added to apl
2024-09-03 CPM initial commit
2024-10-21 integrated cp/m into A64
2024-11-07 cpm full BIOS incl. disk support first draft
2024-11-10 fixed bug when entering first line would cause edit to hang
2024-11-22 add comments; fix ReadS bug
2024-11-22 Fixed bug in sys_rnd
2024-11-22 Changed Open to a function. Fixed the bug in the function evaluation algorithm
    An expression containing a function would only get evaluated if the function was at the beginning of the expression.
2024-11-23 Various
2024-11-23 Fixed the DOS functions in sys to stop them from freezing the program
2024-12-14 corrected various bugs in the TellyMate driver
2024-12-14 simplified the build script
2024-12-15 bringing A180 in sync with the main branch
2024-12-19 Added the Size() and ChDir() functions
2024-12-19 Added the MkDir() function
2024-12-19 Allow to call functions like procedures
2024-12-19 Added the Delete() function
2024-12-19 Added Eof() function
2024-12-21 added the Cmp() procedure
2024-12-26 Various DOS and string functions in APL
2025-01-04 Added the SubStr procedure
2025-01-12 Fixing error with parsing negative values
2025-01-15 Added MaxX and MaxY
2025-01-15 adding the 4x7 font
2025-01-15 Size() returns a number too large by 1
2025-01-15 Eof() returns TRUE one byte too late.
2025-01-15 Added all error messages to dos_printError
2025-01-17 added character literal support
2025-01-17 Fixed MaxY() returning the value of MaxX()
2025-01-17 Fixes MkDir() not terminating the dir name with a 0
2025-01-17 Added the ? operator
2025-01-26 modified the CF base address
2025-01-26 added click back to the keyboard driver
2025-01-28 added the ShowCursor and HideCursor procedures
2025-02-04 Added CF support/setup to the boot routine
2025-02-11 Added the KeyPressed() function
2025-03-08 Switched from 512 to 256 byte sectors
2025-03-15 Added syntax error reporting
2025-04-06 added move and copy commands
2025-04-06 fixed varius bugs
2025-04-13 completed drums prototype
2025-04-23 Moved the BitmappedVgaCard schematics to a new folder
2025-05-16 Fixed bug with minus with parenthesis. Separated run and apl commands
2025-05-17 somewhat functional dungeon generation
2025-05-27 Removed the necessity to use variable names in the NEXT statement
2025-06-08 Refactor: processing the input statement by statement
2025-06-13 Fixed the SyntaxError when END_B is reached
2025-06-13 Added autoexec support
2025-06-16 added source line numbers in compiled code
2025-09-07 final commit on old computer
2025-11-13 Sorted out the scrolling bug
2025-11-13 modified the assembler executable path
2025-11-17 fixed a bug in putchar that causes a to be destroyed
    also moved the video memory start down by two lines to avoid image skew
2025-11-17 removed dead code
2025-11-17 moved the display area one char to the right
    Also, added colour codes for compatibility with colourvga
2025-12-22 Updating Altair Basic 8k
2025-12-27 font refinements
2025-12-28 updated fontvisualiser to support different font widths
2026-03-29 Fixing bugs in the 80 column driver
2026-03-29 Added man and tar commands
2026-03-29 colour VGA test ROM
2026-03-29 accomodate all kinds of CF card faults
2026-03-29 Added colour definitions
2026-03-29 Basic updates
2026-03-31 Fixed memory clearing bug
2026-04-05 added a slash at the beggining of folder names in ls command
2026-04-05 added 16bit copy and fill commands
    also, lots of refactoring
2026-04-06 added the jump table
2026-04-06 making the jump table compile
2026-04-06 make tar load work
2026-04-12 fixed a bug with leading zero in front of the FOR bytecode
    Added man page
2026-04-12 corrected formatting
2026-04-12 MAN to use the existing TempDirName DOS variable
2026-04-12 fixed line end characters
2026-04-17 Changed TM to using x1 clock
2026-04-17 Added a DART init command
2026-04-17 Added a serial connector section
2026-04-18 removing unused device drivers
2026-04-21 removed redundant register transfers
2026-05-09 Removing startup code that is moved to autoexec
2026-05-09 support address as parameter for the mon command
2026-06-05 Refactored NMI handler
    Also, fixed the greeting reverse colour bug
2026-06-05 fixed the cursor tracking bugs
    also, moved the display down by 6 screen lines to avoid flicker
2026-06-05 removed colour definitions
    ...that were supposed to go to to pal.asm
2026-06-05 jump table incremental updates
    still not the final version
2026-06-05 added colours to the interface
2026-06-05 refactor
    - formatting changes
    - stop using NMIs
    - stop using getChar
2026-06-05 4K altair basic
